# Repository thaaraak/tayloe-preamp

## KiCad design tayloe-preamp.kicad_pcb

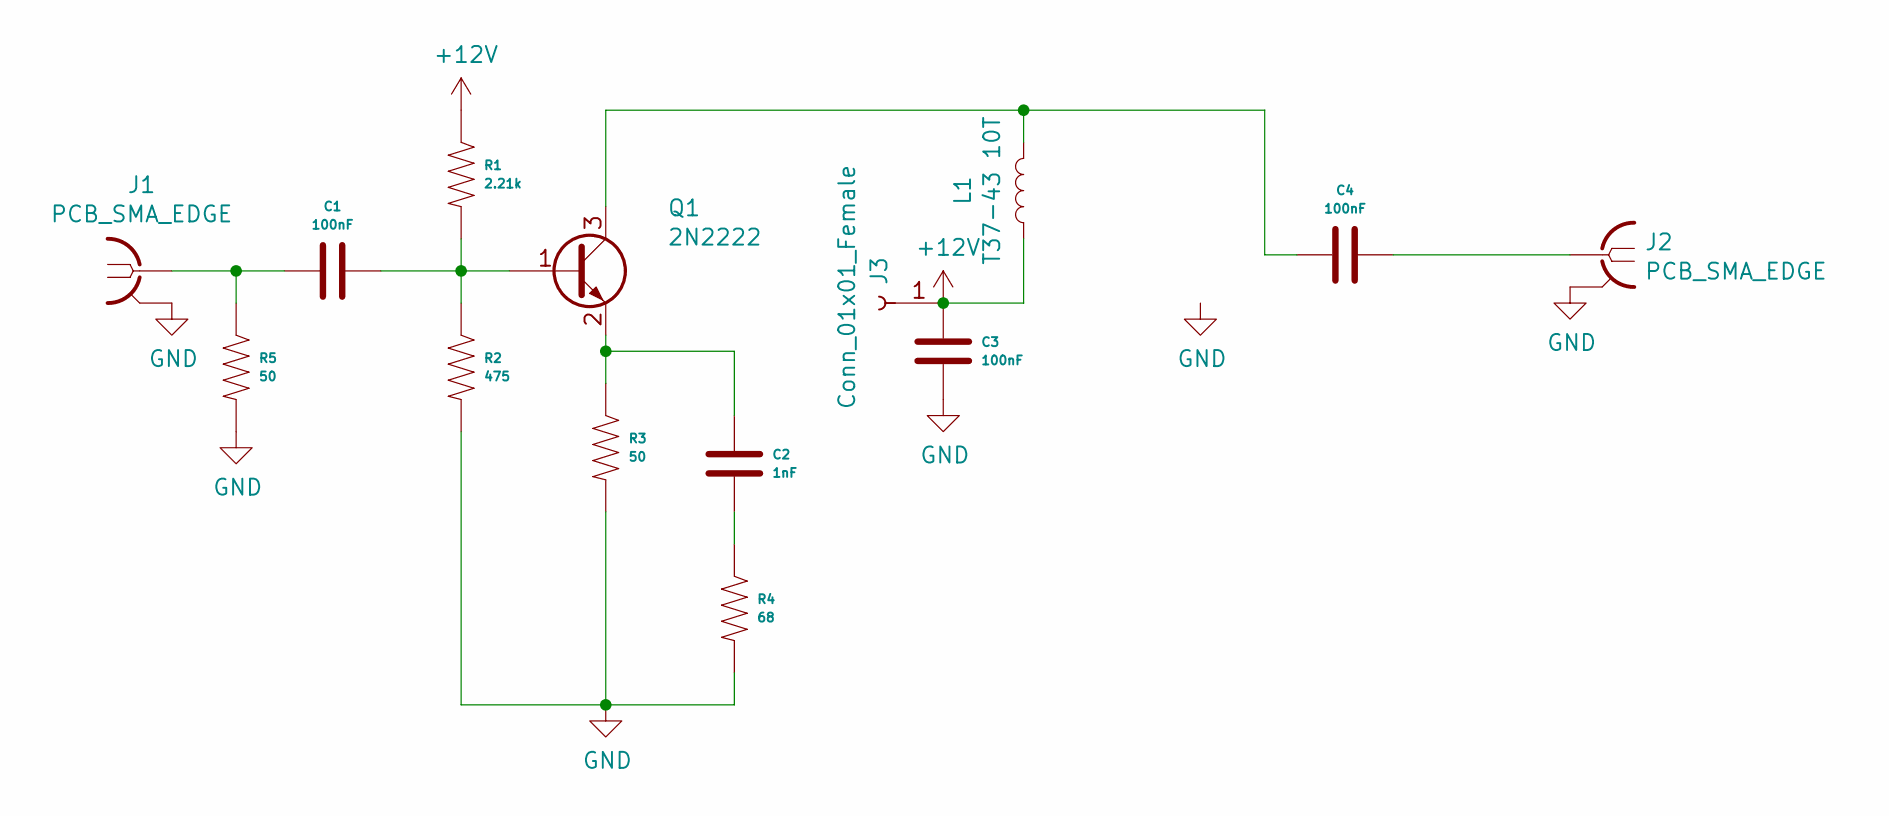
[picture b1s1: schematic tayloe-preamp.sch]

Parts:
C1, C3, C4: 100nF; Capacitor 1206
C2: 1nF; Capacitor 1206
J1, J2: PCB_SMA_EDGE; PCB-SMA-EDGE
J3: Conn_01x01_Female; PinHeader_1x01_P2.54mm_Vertical
L1: T37-43 10T; T37_Inductor
Q1: 2N2222; SOT-23
R1: 2.21k; Resistor 1206
R2: 475; Resistor 1206
R3, R5: 50; Resistor 1206
R4: 68; Resistor 1206

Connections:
+12V: C3.1, J3.1, L1.1, R1.1
GND: C3.2, J1.2, J2.2, R2.2, R3.2, R4.2, R5.2
unnamed: C1.1, Q1.1 (B), R1.2, R2.1
unnamed: C1.2, J1.1, R5.1
unnamed: C2.1, Q1.2 (E), R3.1
unnamed: C2.2, R4.1
unnamed: C4.1, J2.1
unnamed: C4.2, L1.2, Q1.3 (C)

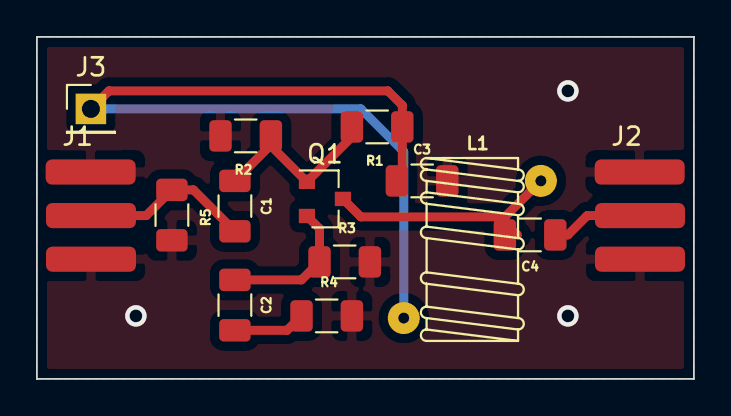
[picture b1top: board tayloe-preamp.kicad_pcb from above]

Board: 2 copper layers, 36.5 x 19.0 mm, 14 parts (0 on the bottom side), 8 nets.

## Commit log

2022-12-16 added 50 ohm input
2022-12-16 changed to inductor
